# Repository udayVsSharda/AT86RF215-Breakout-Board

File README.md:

# AT86RF215-Breakout-Board
AT86RF215 Breakout Board is a **4-layer controlled impedance board with JLCPCB's JLC04161H-3313 Stackup.**  AT86RF215xx is a fully integrated radio transceiver covering 389.5-510MHz / 779-1020MHz / 2400-2483.5MHz. It is configured using the SPI bus to receive and transmit while simultaneously operating the sub-1GHz and 2.4GHz radios.The impedance-matching filter are centered on 896MHz and 2450Mhz, so the design is optimized for the 2.4Ghz ISM and 900Mhz ISM bands. At 900MHz, transmit output power can be programmed upto +14dBm. The IQ interface with a sampling frequency of up to 4MHz gives it a decent bandwidth. I did not include manufacturing files(except BOM), but they can be easily obtained by following [JLCPCB Guide.](https://jlcpcb.com/help/article/how-to-generate-gerber-and-drill-files-in-kicad-9)  

[View the full PDF Schematic](https://github.com/udayVsSharda/AT86RF215-Breakout-Board/blob/main/Documents/Schematic%20AT86RF215%20Breakout-Board.pdf)

## IQ Interface
It can also be configured for custom protocols using the 13-bit IQ Interface. Baseband PHY's transceiver can be completely bypassed by feeding IQ data directly to the DAC's using LVDS.The LVDS interface is based on the IEEE standard 1596.3 1996. The LVDS interface of the AT86RF215 has a data rate of 128Mb/s, composed of 16 data bits at 4MHz, for each of the I and Q data streams from the device. The LVDS uses double data rate (DDR), at a clock frequency of 64MHz. This flexibility makes it **useful for custom SDR Application.** The IQ interface can be accessed by soldering a **Molex Connector Part No. 53748-0408** connecting it ing board to board connector ** receptacle Molex Part No. 52991-0408** or similar 0.5mm pitch Board-to-Board Connectors.  

## Credit
[Uday Vivek Singh SHARDA](https://www.linkedin.com/in/uday-vivek-singh-sharda-988475122/)  
EENG2 P2029 ECAM LaSalle Lyon  
[KiCAD 8.0](https://www.kicad.org/)

## License
Hardware design files in this repository are licensed under the CERN-OHL-P-2.0 license.
See the LICENSE file for full terms.

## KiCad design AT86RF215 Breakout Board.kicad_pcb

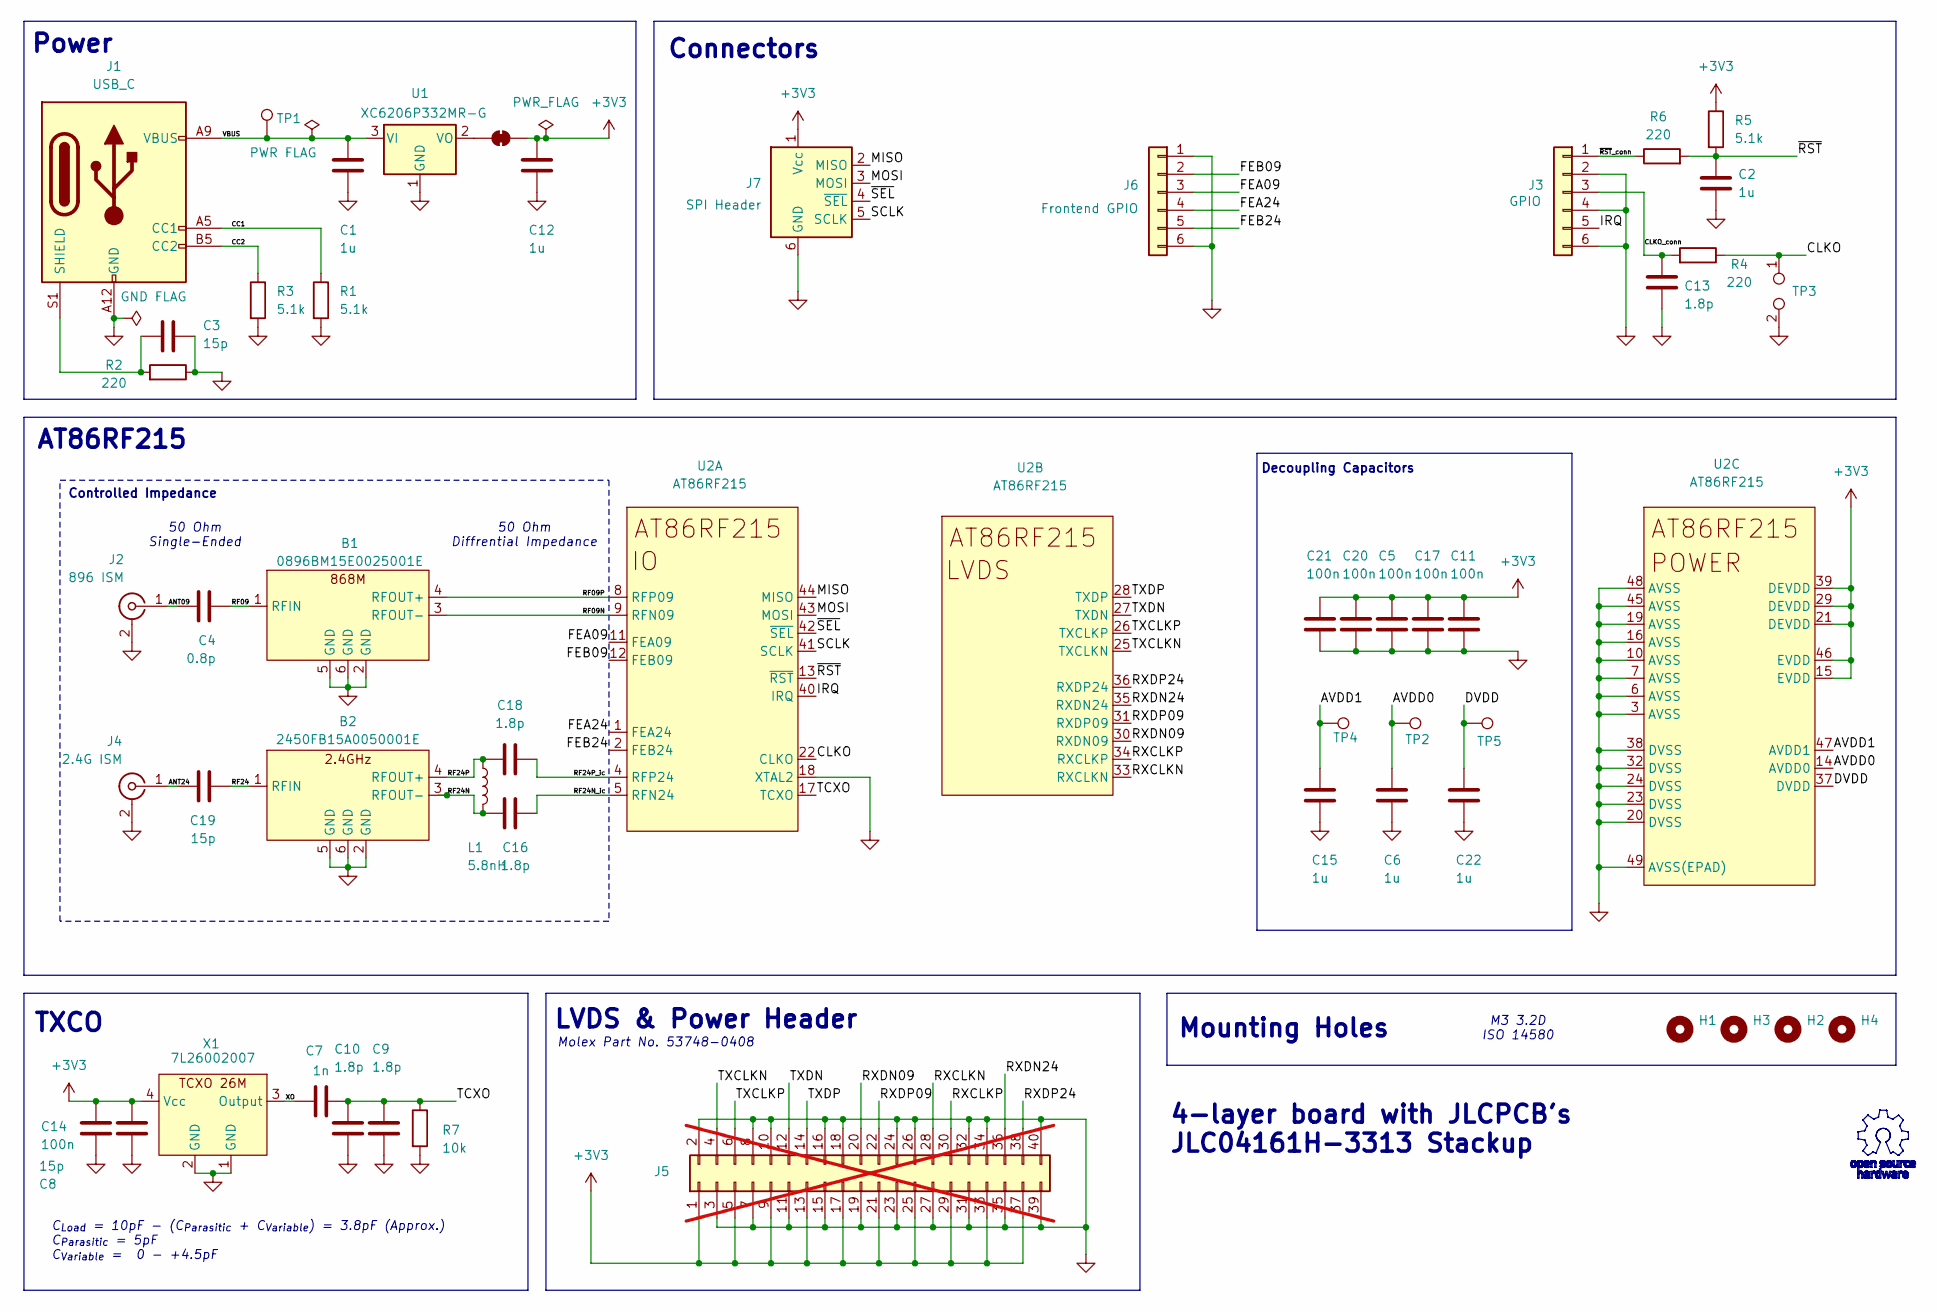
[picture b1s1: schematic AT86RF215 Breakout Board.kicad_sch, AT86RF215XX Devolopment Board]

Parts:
B1: 0896BM15E0025001E; 0896BM15E0025
B2: 2450FB15A0050001E; 0896BM15E0025
C1, C2, C6, C12, C15, C22: 1u; C_0402_1005Metric
C3, C8, C19: 15p; C_0402_1005Metric
C4: 0.8p; C_0402_1005Metric
C5, C11, C14, C17, C20, C21: 100n; C_0402_1005Metric
C7: 1n; C_0402_1005Metric
C9, C10, C13, C16, C18: 1.8p; C_0402_1005Metric
H1, H2, H3, H4: MountingHole; MountingHole_3.2mm_M3_ISO14580
J1: USB_C; USB_C_Receptacle_GCT_USB4125-xx-x-0190_6P_TopMnt_Horizontal
J2: 896 ISM; BWSMA-KE-Z001
J3: GPIO; PinHeader_1x06_P2.54mm_Vertical
J4: 2.4G ISM; BWSMA-KE-Z001
J5: Molex 53748-0408; Molex_SlimStack_53748-0408_2x20_P0.50mm_Vertical; not fitted
J6: Frontend GPIO; PinHeader_1x06_P2.54mm_Vertical
J7: SPI Header; PinHeader_1x06_P2.54mm_Vertical
JP1: SolderJumper_2_Bridged; SolderJumper-2_P1.3mm_Bridged_RoundedPad1.0x1.5mm
L1: 5.8nH; L_0402_1005Metric
R1, R3, R5: 5.1k; R_0603_1608Metric
R2, R4, R6: 220; R_0603_1608Metric
R7: 10k; R_0603_1608Metric
TP1: VBUS; TestPoint_Pad_D1.0mm
TP2: AVDD0; TestPoint_Pad_D1.0mm
TP3: CLKO; PinHeader_1x02_P2.54mm_Vertical
TP4: AVDD1; TestPoint_Pad_D1.0mm
TP5: DVDD; TestPoint_Pad_D1.0mm
U1: XC6206P332MR-G; SOT-23-3
U2: AT86RF215
X1: 7L26002007

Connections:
+3V3: C5.1, C8.2, C11.1, C12.1, C14.1, C17.1, C20.1, C21.1, J5.1, J5.5, J5.9, J5.13, J5.17, J5.21, J5.25, J5.29, J5.33, J5.37, J7.1 (Vcc), JP1.1 (A), R5.1, U2.15 (EVDD), U2.21 (DEVDD), U2.29 (DEVDD), U2.39 (DEVDD), U2.46 (EVDD), X1.4 (Vcc)
/ANT09: C4.2, J2.1 (In)
/ANT24: C19.2, J4.1 (In)
/AVDD0: C6.1, TP2.1, U2.14 (AVDD0)
/AVDD1: C15.1, TP4.1, U2.47 (AVDD1)
/CC1: J1.A5 (CC1), R1.1
/CC2: J1.B5 (CC2), R3.1
/CLKO: R4.1, TP3.1, U2.22 (CLKO)
/CLKO_conn: C13.2, J3.3, R4.2
/DVDD: C22.1, TP5.1, U2.37 (DVDD)
/FEA09: J6.3, U2.11 (FEA09)
/FEA24: J6.4, U2.1 (FEA24)
/FEB09: J6.2, U2.12 (FEB09)
/FEB24: J6.5, U2.2 (FEB24)
/IRQ: J3.5, U2.40 (IRQ)
/MISO: J7.2 (MISO), U2.44 (MISO)
/MOSI: J7.3 (MOSI), U2.43 (MOSI)
/RF09: B1.1 (RFIN), C4.1
/RF09N: B1.3 (RFOUT-), U2.9 (RFN09)
/RF09P: B1.4 (RFOUT+), U2.8 (RFP09)
/RF24: B2.1 (RFIN), C19.1
/RF24N: B2.3 (RFOUT-), C16.1, L1.2
/RF24N_ic: C16.2, U2.5 (RFN24)
/RF24P: B2.4 (RFOUT+), C18.1, L1.1
/RF24P_ic: C18.2, U2.4 (RFP24)
/RXCLKN: J5.28, U2.33 (RXCLKN)
/RXCLKP: J5.30, U2.34 (RXCLKP)
/RXDN09: J5.20, U2.30 (RXDN09)
/RXDN24: J5.36, U2.35 (RXDN24)
/RXDP09: J5.22, U2.31 (RXDP09)
/RXDP24: J5.38, U2.36 (RXDP24)
/SCLK: J7.5 (SCLK), U2.41 (SCLK)
/TCXO: C7.2, C9.2, C10.2, R7.1, U2.17 (TCXO)
/TXCLKN: J5.4, U2.25 (TXCLKN)
/TXCLKP: J5.6, U2.26 (TXCLKP)
/TXDN: J5.12, U2.27 (TXDN)
/TXDP: J5.14, U2.28 (TXDP)
/VBUS: C1.1, J1.A9 (VBUS), J1.B9 (VBUS), TP1.1, U1.3 (VI)
/XO: C7.1, X1.3 (Output)
/~RST: C2.1, R5.2, R6.2, U2.13 (~RST)
/~RST_conn: J3.1, R6.1
/~SEL: J7.4 (~SEL), U2.42 (~SEL)
GND: B1.2 (GND), B1.5 (GND), B1.6 (GND), B2.2 (GND), B2.5 (GND), B2.6 (GND), C1.2, C2.2, C3.2, C5.2, C6.2, C8.1, C9.1, C10.1, C11.2, C12.2, C13.1, C14.2, C15.2, C17.2, C20.2, C21.2, C22.2, J1.A12 (GND), J1.B12 (GND), J2.2 (Ext), J3.2, J3.4, J3.6, J4.2 (Ext), J5.2, J5.3, J5.7, J5.8, J5.10, J5.11, J5.15, J5.16, J5.18, J5.19, J5.23, J5.24, J5.26, J5.27, J5.31, J5.32, J5.34, J5.35, J5.39, J5.40, J6.1, J6.6, J7.6 (GND), R1.2, R2.1, R3.2, R7.2, TP3.2, U1.1 (GND), U2.3 (AVSS), U2.6 (AVSS), U2.7 (AVSS), U2.10 (AVSS), U2.16 (AVSS), U2.18 (XTAL2), U2.19 (AVSS), U2.20 (DVSS), U2.23 (DVSS), U2.24 (DVSS), U2.32 (DVSS), U2.38 (DVSS), U2.45 (AVSS), U2.48 (AVSS), U2.49 (AVSS(EPAD)), X1.1 (GND), X1.2 (GND)
unnamed: C3.1, J1.S1 (SHIELD), R2.2
unnamed: JP1.2 (B), U1.2 (VO)

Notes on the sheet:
LVDS & Power Header
Power
C_{Load} = 10pF - (C_{Parasitic} + C_{Variable}) = 3.8pF (Approx.) C_{Parasitic} = 5pF C_{Variable} = 0 - +4.5pF
Connectors
AT86RF215
50 Ohm Diffrential Impedance
TXCO
Controlled Impedance
50 Ohm Single-Ended
Decoupling Capacitors
4-layer board with JLCPCB's JLC04161H-3313 Stackup
Molex Part No. 53748-0408
M3 3.2D ISO 14580
Mounting Holes

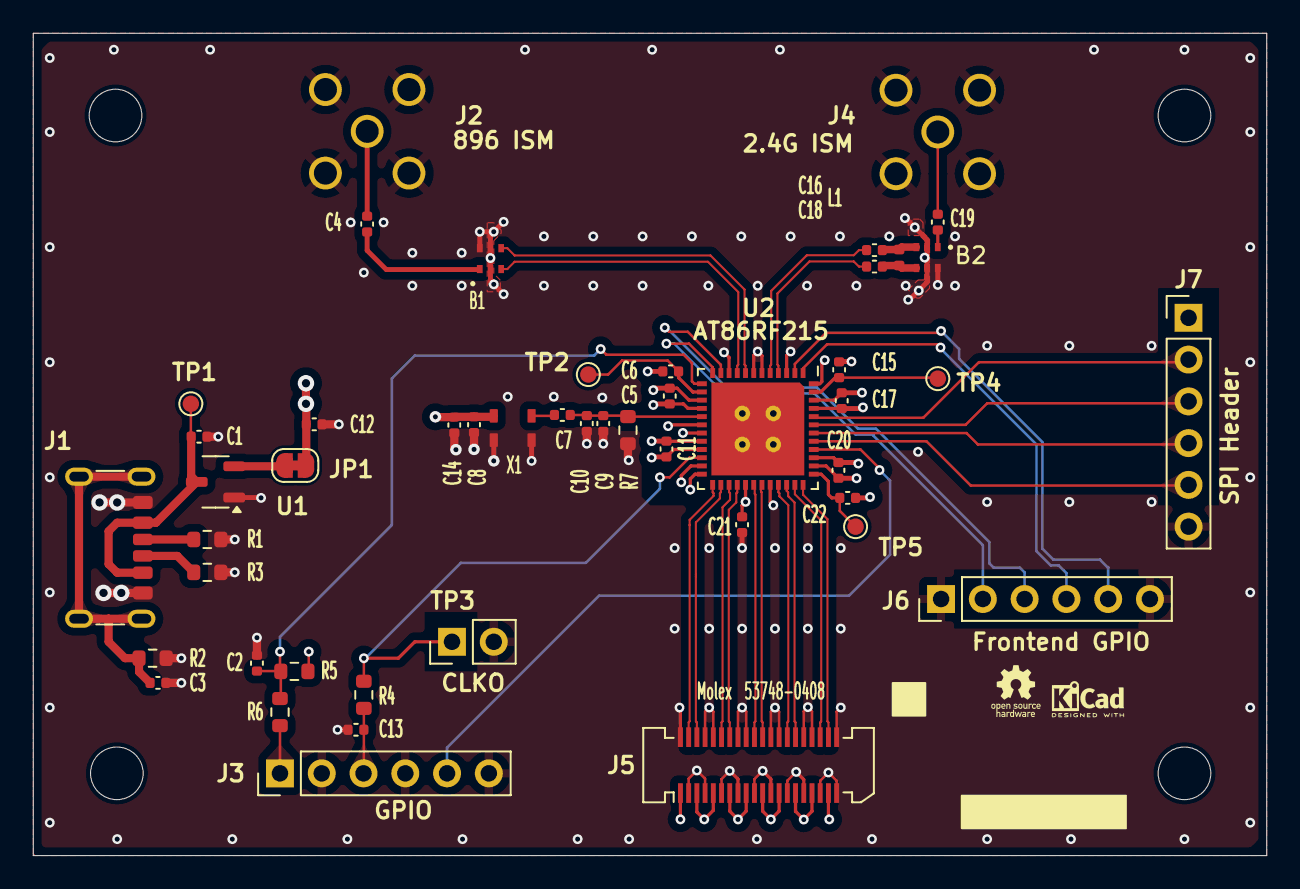
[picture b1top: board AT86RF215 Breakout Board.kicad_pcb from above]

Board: 4 copper layers, 75.0 x 50.0 mm, 52 parts (0 on the bottom side), 45 nets.

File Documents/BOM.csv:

Comment,Designator,Footprint,JLCPCB Part#
0896BM15E0025001E,B1,0896BM15E0025,C17271374
2450FB15A0050001E,B2,0896BM15E0025,C17352285
1u,"C1,C2,C6,C12,C15,C22",C_0402_1005Metric,C52923
15p,"C3,C8,C19",C_0402_1005Metric,C1548
0.8p,C4,C_0402_1005Metric,C88902
100n,"C5,C11,C14,C17,C20,C21",C_0402_1005Metric,C307331
1n,C7,C_0402_1005Metric,C1523
1.8p,"C9,C10,C13,C16,C18",C_0402_1005Metric,C76903
USB_C,J1,TYPE-C-6P,C19274014
5.8nH,L1,L_0402_1005Metric,C576549
5.1k,"R1,R3,R5",R_0603_1608Metric,C23186
220,"R2,R4,R6",R_0603_1608Metric,C22962
10k,R7,R_0603_1608Metric,C2906982
XC6206P332MR-G,U1,SOT-23-3,C5446
AT86RF215,U2,JEDEC MO-220 VKKD-4,C2151562
7L26002007,X1,7L26002007,C409249

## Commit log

2026-02-13 Create LICENCE
2026-02-13 Rename AT86RF215 Breakout Board.pdf to Documents/AT86RF215 Breakout Board.pdf
2026-02-13 Rename IQ-LVDS-Connections-Diagram .png to IQ-LVDS-Connections-Diagram.png
2026-02-13 Rename AT86RF215 Breakout Board.pdf to PDF- Schematic AT86RF215 Breakout-Board.pdf
2026-02-13 Rename PDF- Schematic AT86RF215 Breakout-Board.pdf to PDF- Schematic AT86RF215 Breakout-Board.pdf
2026-02-13 Rename PDF- Schematic AT86RF215 Breakout-Board.pdf to Schematic AT86RF215 Breakout-Board.pdf
2026-02-13 added local symbol and footprint libs
